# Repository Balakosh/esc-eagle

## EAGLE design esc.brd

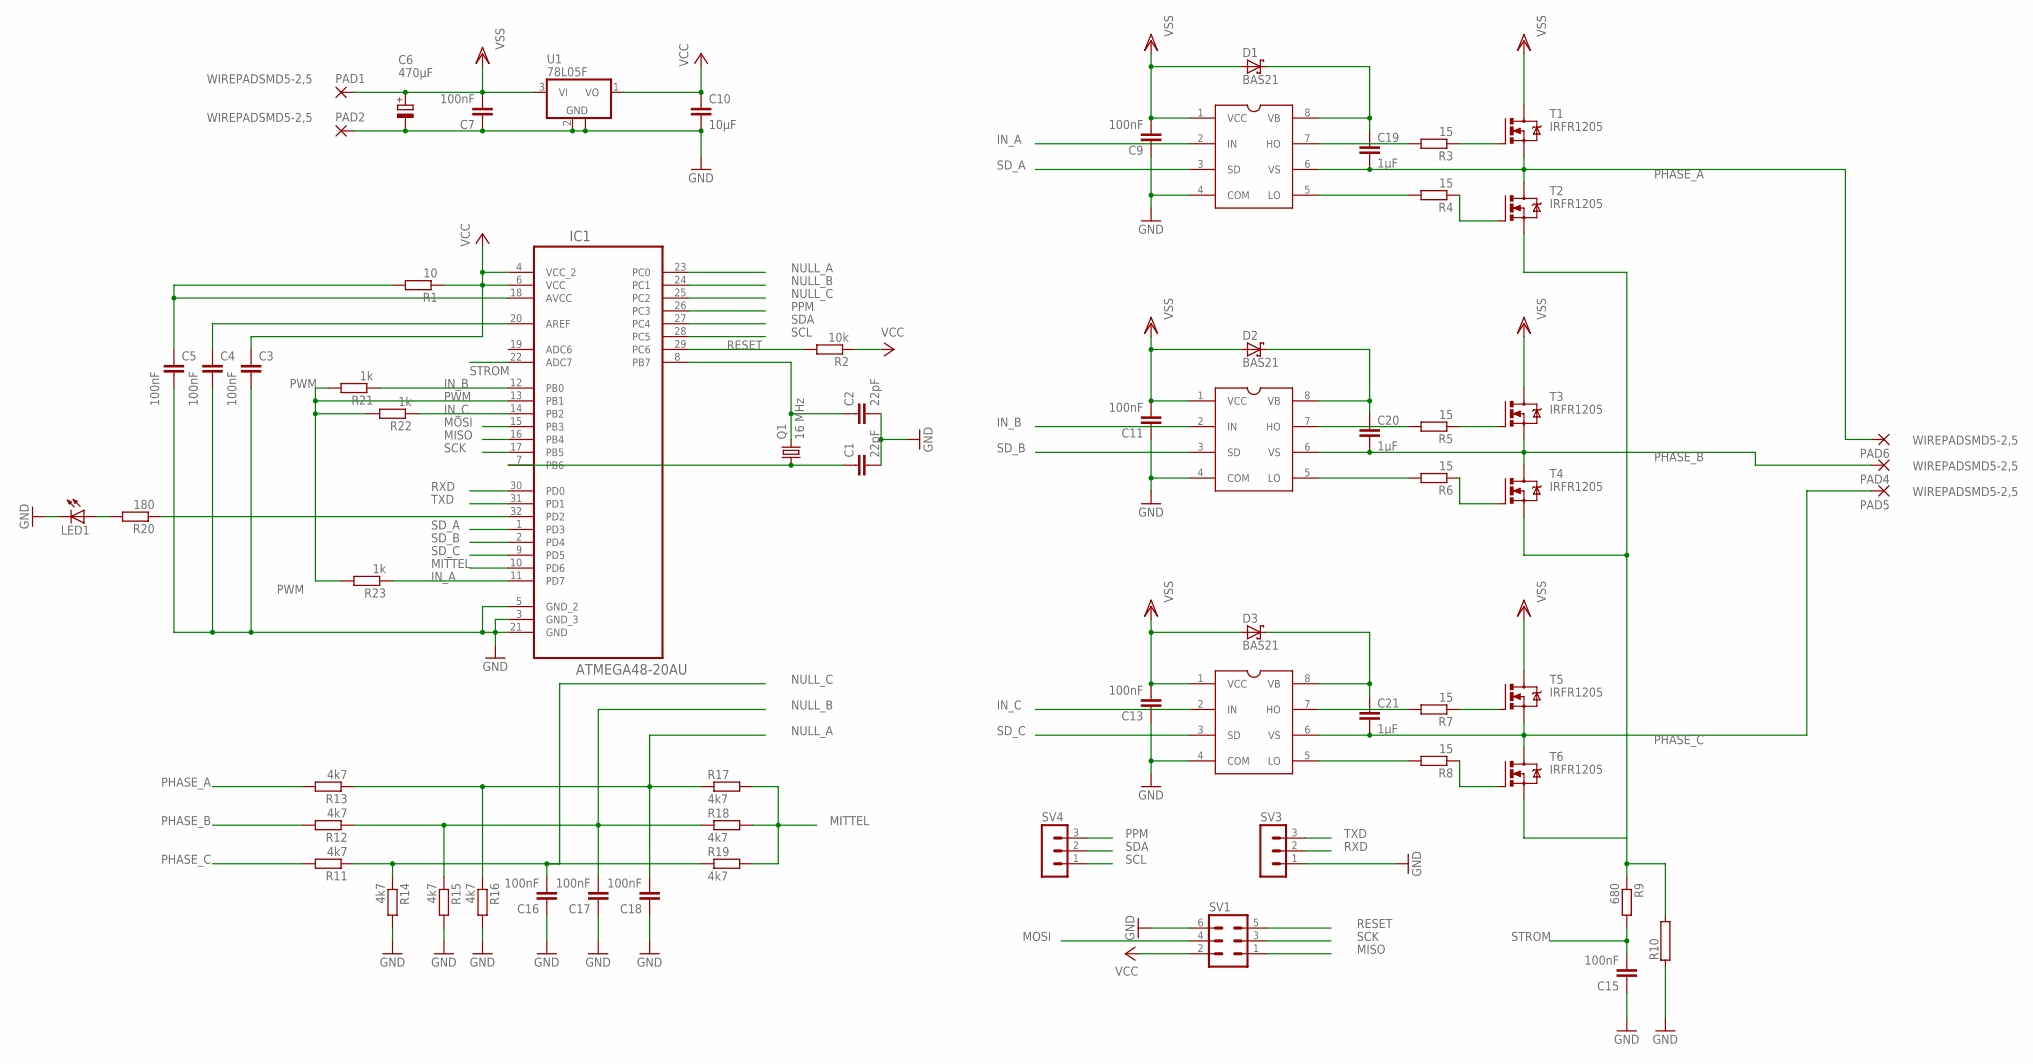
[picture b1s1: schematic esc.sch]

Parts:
C1, C2: 22pF; C1206
C3, C4, C5, C7, C9, C11, C13, C15, C16, C17, C18: 100nF; C1206
C6: 470µF; E5-10,5
C10: 10µF; C1206
C19, C20, C21: 1µF; C1206
D1, D2, D3: BAS21; SOT23
IC1: ATMEGA48-20AU; QFP80P900X900X120-32N
LED1: LEDCHIPLED_1206; CHIPLED_1206
PAD1, PAD2, PAD4, PAD5, PAD6: WIREPADSMD5-2,5; 5-2,5
Q1: 16 MHz; HC49UP
R1: 10; R1206
R2: 10k; R1206
R3, R4, R5, R6, R7, R8: 15; R1206
R9: 680; R1206
R10: RCA5150; CA5150
R11, R12, R13, R14, R15, R16, R17, R18, R19: 4k7; R1206
R20: 180; R1206
R21, R22, R23: 1k; R1206
SV1: ML6
SV3, SV4: MA03-1
T1, T2, T3, T4, T5, T6: IRFR1205; DPACK
U1: 78L05F; SOT89
U$1, U$2, U$3: IR2104S

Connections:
GND: C1.2, C2.2, C3.2, C4.2, C5.2, C6.-, C7.1, C9.1, C10.2, C11.1, C13.1, C15.1, C16.1, C17.1, C18.1, IC1.3 (GND_3), IC1.5 (GND_2), IC1.21 (GND), LED1.C, PAD2.1, R10.1, R14.2, R15.2, R16.2, SV1.6, SV3.1, U1.2 (GND), U1.2@1 (GND), U$1.4 (COM), U$2.4 (COM), U$3.4 (COM)
IN_A: IC1.11 (PD7), R23.1, U$1.2 (IN)
IN_B: IC1.12 (PB0), R21.1, U$2.2 (IN)
IN_C: IC1.14 (PB2), R22.1, U$3.2 (IN)
MISO: IC1.16 (PB4), SV1.1
MITTEL: IC1.10 (PD6), R17.2, R18.2, R19.2
MOSI: IC1.15 (PB3), SV1.4
unnamed: C1.1, IC1.7 (PB6), Q1.1
unnamed: C5.1, IC1.18 (AVCC), R1.2
unnamed: C2.1, IC1.8 (PB7), Q1.2
unnamed: C4.1, IC1.20 (AREF)
unnamed: R3.1, T1.1 (G)
unnamed: R4.1, T2.1 (G)
unnamed: R9.1, R10.2, T2.3 (S), T4.3 (S), T6.3 (S)
unnamed: C20.1, D2.3 (C), U$2.8 (VB)
unnamed: C19.1, D1.3 (C), U$1.8 (VB)
unnamed: R5.2, U$2.7 (HO)
unnamed: R3.2, U$1.7 (HO)
unnamed: R4.2, U$1.5 (LO)
unnamed: R6.2, U$2.5 (LO)
unnamed: R5.1, T3.1 (G)
unnamed: R6.1, T4.1 (G)
unnamed: LED1.A, R20.2
unnamed: C21.1, D3.3 (C), U$3.8 (VB)
unnamed: R7.2, U$3.7 (HO)
unnamed: R8.2, U$3.5 (LO)
unnamed: R7.1, T5.1 (G)
unnamed: R8.1, T6.1 (G)
unnamed: IC1.32 (PD2), R20.1
NULL_A: C18.2, IC1.23 (PC0), R13.1, R16.1, R17.1
NULL_B: C17.2, IC1.24 (PC1), R12.1, R15.1, R18.1
NULL_C: C16.2, IC1.25 (PC2), R11.1, R14.1, R19.1
PHASE_A: C19.2, PAD6.1, R13.2, T1.3 (S), T2.2 (D), U$1.6 (VS)
PHASE_B: C20.2, PAD4.1, R12.2, T3.3 (S), T4.2 (D), U$2.6 (VS)
PHASE_C: C21.2, PAD5.1, R11.2, T5.3 (S), T6.2 (D), U$3.6 (VS)
PPM: IC1.26 (PC3), SV4.3
PWM: IC1.13 (PB1), R21.2, R22.2, R23.2
RESET: IC1.29 (PC6), R2.2, SV1.5
RXD: IC1.30 (PD0), SV3.2
SCK: IC1.17 (PB5), SV1.3
SCL: IC1.28 (PC5), SV4.1
SDA: IC1.27 (PC4), SV4.2
SD_A: IC1.1 (PD3), U$1.3 (SD)
SD_B: IC1.2 (PD4), U$2.3 (SD)
SD_C: IC1.9 (PD5), U$3.3 (SD)
STROM: C15.2, IC1.22 (ADC7), R9.2
TXD: IC1.31 (PD1), SV3.3
VCC: C3.1, C10.1, IC1.4 (VCC_2), IC1.6 (VCC), R1.1, R2.1, SV1.2, U1.1 (VO)
VSS: C6.+, C7.2, C9.2, C11.2, C13.2, D1.1 (A), D2.1 (A), D3.1 (A), PAD1.1, T1.2 (D), T3.2 (D), T5.2 (D), U1.3 (VI), U$1.1 (VCC), U$2.1 (VCC), U$3.1 (VCC)

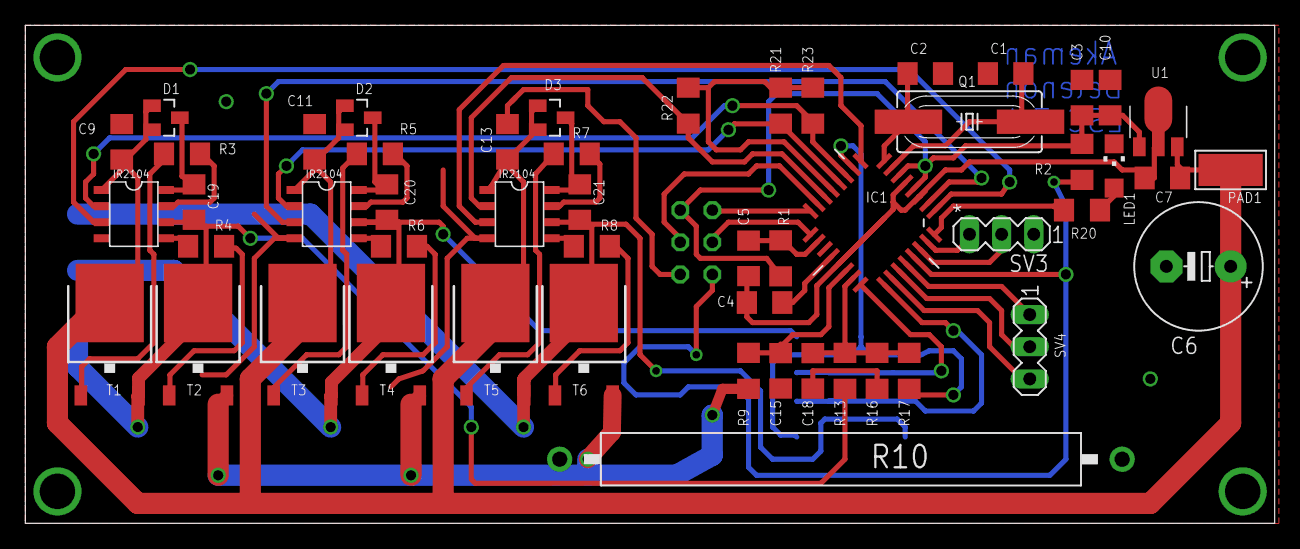
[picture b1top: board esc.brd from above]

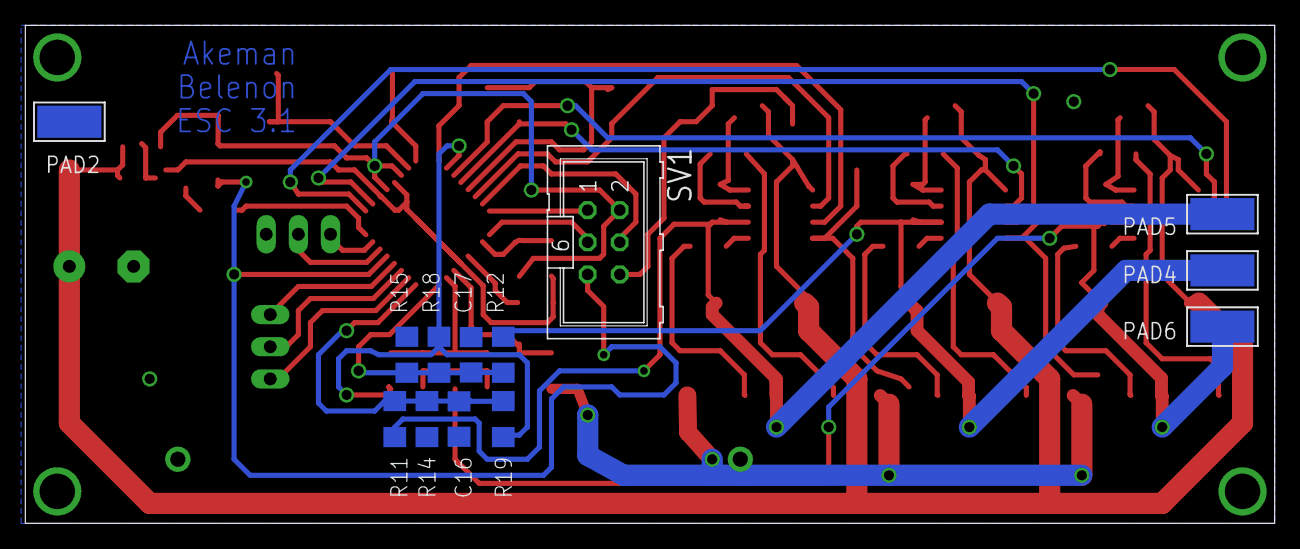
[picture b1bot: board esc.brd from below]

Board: 2 copper layers, 98.7 x 39.3 mm, 65 parts (13 on the bottom side), 49 nets.

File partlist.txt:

Partlist

Exported from esc.sch at 18.12.2014 14:14:19

EAGLE Version 6.3.0 Copyright (c) 1988-2012 CadSoft

Assembly variant: 

Part     Value          Device          Package               Library                       Sheet

C1       22pF           C-EUC1206       C1206                 rcl                           1
C2       22pF           C-EUC1206       C1206                 rcl                           1
C3       100nF          C-EUC1206       C1206                 rcl                           1
C4       100nF          C-EUC1206       C1206                 rcl                           1
C5       100nF          C-EUC1206       C1206                 rcl                           1
C6       470µF          CPOL-EUE5-10.5  E5-10,5               rcl                           1
C7       100nF          C-EUC1206       C1206                 rcl                           1
C9       100nF          C-EUC1206       C1206                 rcl                           1
C10      10µF           C-EUC1206       C1206                 rcl                           1
C11      100nF          C-EUC1206       C1206                 rcl                           1
C13      100nF          C-EUC1206       C1206                 rcl                           1
C15      100nF          C-EUC1206       C1206                 rcl                           1
C16      100nF          C-EUC1206       C1206                 rcl                           1
C17      100nF          C-EUC1206       C1206                 rcl                           1
C18      100nF          C-EUC1206       C1206                 rcl                           1
C19      1µF            C-EUC1206       C1206                 rcl                           1
C20      1µF            C-EUC1206       C1206                 rcl                           1
C21      1µF            C-EUC1206       C1206                 rcl                           1
D1       BAS21          BAS40           SOT23                 diode                         1
D2       BAS21          BAS40           SOT23                 diode                         1
D3       BAS21          BAS40           SOT23                 diode                         1
IC1      78L05F         78L05F          SOT89                 linear                        1
LED1                    LEDCHIPLED_1206 CHIPLED_1206          led                           1
Q1       16 MHz         CRYSTALHC49UP   HC49UP                crystal                       1
R1       10             R-EU_R1206      R1206                 rcl                           1
R2       10k            R-EU_R1206      R1206                 rcl                           1
R3       15             R-EU_R1206      R1206                 rcl                           1
R4       15             R-EU_R1206      R1206                 rcl                           1
R5       15             R-EU_R1206      R1206                 rcl                           1
R6       15             R-EU_R1206      R1206                 rcl                           1
R7       15             R-EU_R1206      R1206                 rcl                           1
R8       15             R-EU_R1206      R1206                 rcl                           1
R9       680            R-EU_R1206      R1206                 rcl                           1
R10                     RAC01           AC01                  resistor-power                1
R11      4k7            R-EU_R1206      R1206                 rcl                           1
R12      4k7            R-EU_R1206      R1206                 rcl                           1
R13      4k7            R-EU_R1206      R1206                 rcl                           1
R14      4k7            R-EU_R1206      R1206                 rcl                           1
R15      4k7            R-EU_R1206      R1206                 rcl                           1
R16      4k7            R-EU_R1206      R1206                 rcl                           1
R17      4k7            R-EU_R1206      R1206                 rcl                           1
R18      4k7            R-EU_R1206      R1206                 rcl                           1
R19      4k7            R-EU_R1206      R1206                 rcl                           1
R20      180            R-EU_R1206      R1206                 rcl                           1
SV1                     ML6             ML6                   con-ml                        1
SV2                     ML6             ML6                   con-ml                        1
T1       IRFR1205       IRFR1205        DPACK                 IRF                           1
T2       IRFR1205       IRFR1205        DPACK                 IRF                           1
T3       IRFR1205       IRFR1205        DPACK                 IRF                           1
T4       IRFR1205       IRFR1205        DPACK                 IRF                           1
T5       IRFR1205       IRFR1205        DPACK                 IRF                           1
T6       IRFR1205       IRFR1205        DPACK                 IRF                           1
U$1      IR2104S        IR2104S         IR2104S               ir-2104                       1
U$2      IR2104S        IR2104S         IR2104S               ir-2104                       1
U$3      IR2104S        IR2104S         IR2104S               ir-2104                       1
U1       ATMEGA48-20AU  ATMEGA48-20AU   QFP80P900X900X120-32N Atmel_By_element14_Batch_1-00 1
X1                      W237-102        W237-102              con-wago-500                  1
X2                      W237-103        W237-103              con-wago-500                  1

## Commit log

2015-03-17 inital commit
2015-03-21 ppm via, phase c fixed
2015-03-21 changed clearences to 18 mil
2015-03-21 ISP restrict
2015-03-25 Added value to r1 and tRestrict under Quarz
2015-06-02 ISP mirror
2015-06-02 Added design rules
2015-08-01 esc3 initial commit
2015-08-02 changed smd size of µc
2015-08-02 4 Außenbohrungen und Shunt
2015-08-02 Top optimierung für ätzen
2015-08-02 zweites gnd via
2015-08-02 mosfet leitung auf 1.6
2015-08-02 Namen hinzugefügt
2015-08-09 Bestückungsplan smashed
2015-12-24 Changed drill size from 0.6 to 0.8
2015-12-24 minor smash changes
2018-06-14 changes for aisler order
2018-07-09 aisler
2018-11-02 i dont know what changed
2018-11-02 cleaned up repository
2018-11-02 fixed merging errors
